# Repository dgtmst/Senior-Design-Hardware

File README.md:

# Senior-Design-Hardware
Repository for the hardware side of the senior design project
Will primarily be used for PCB design, could use it for other things later

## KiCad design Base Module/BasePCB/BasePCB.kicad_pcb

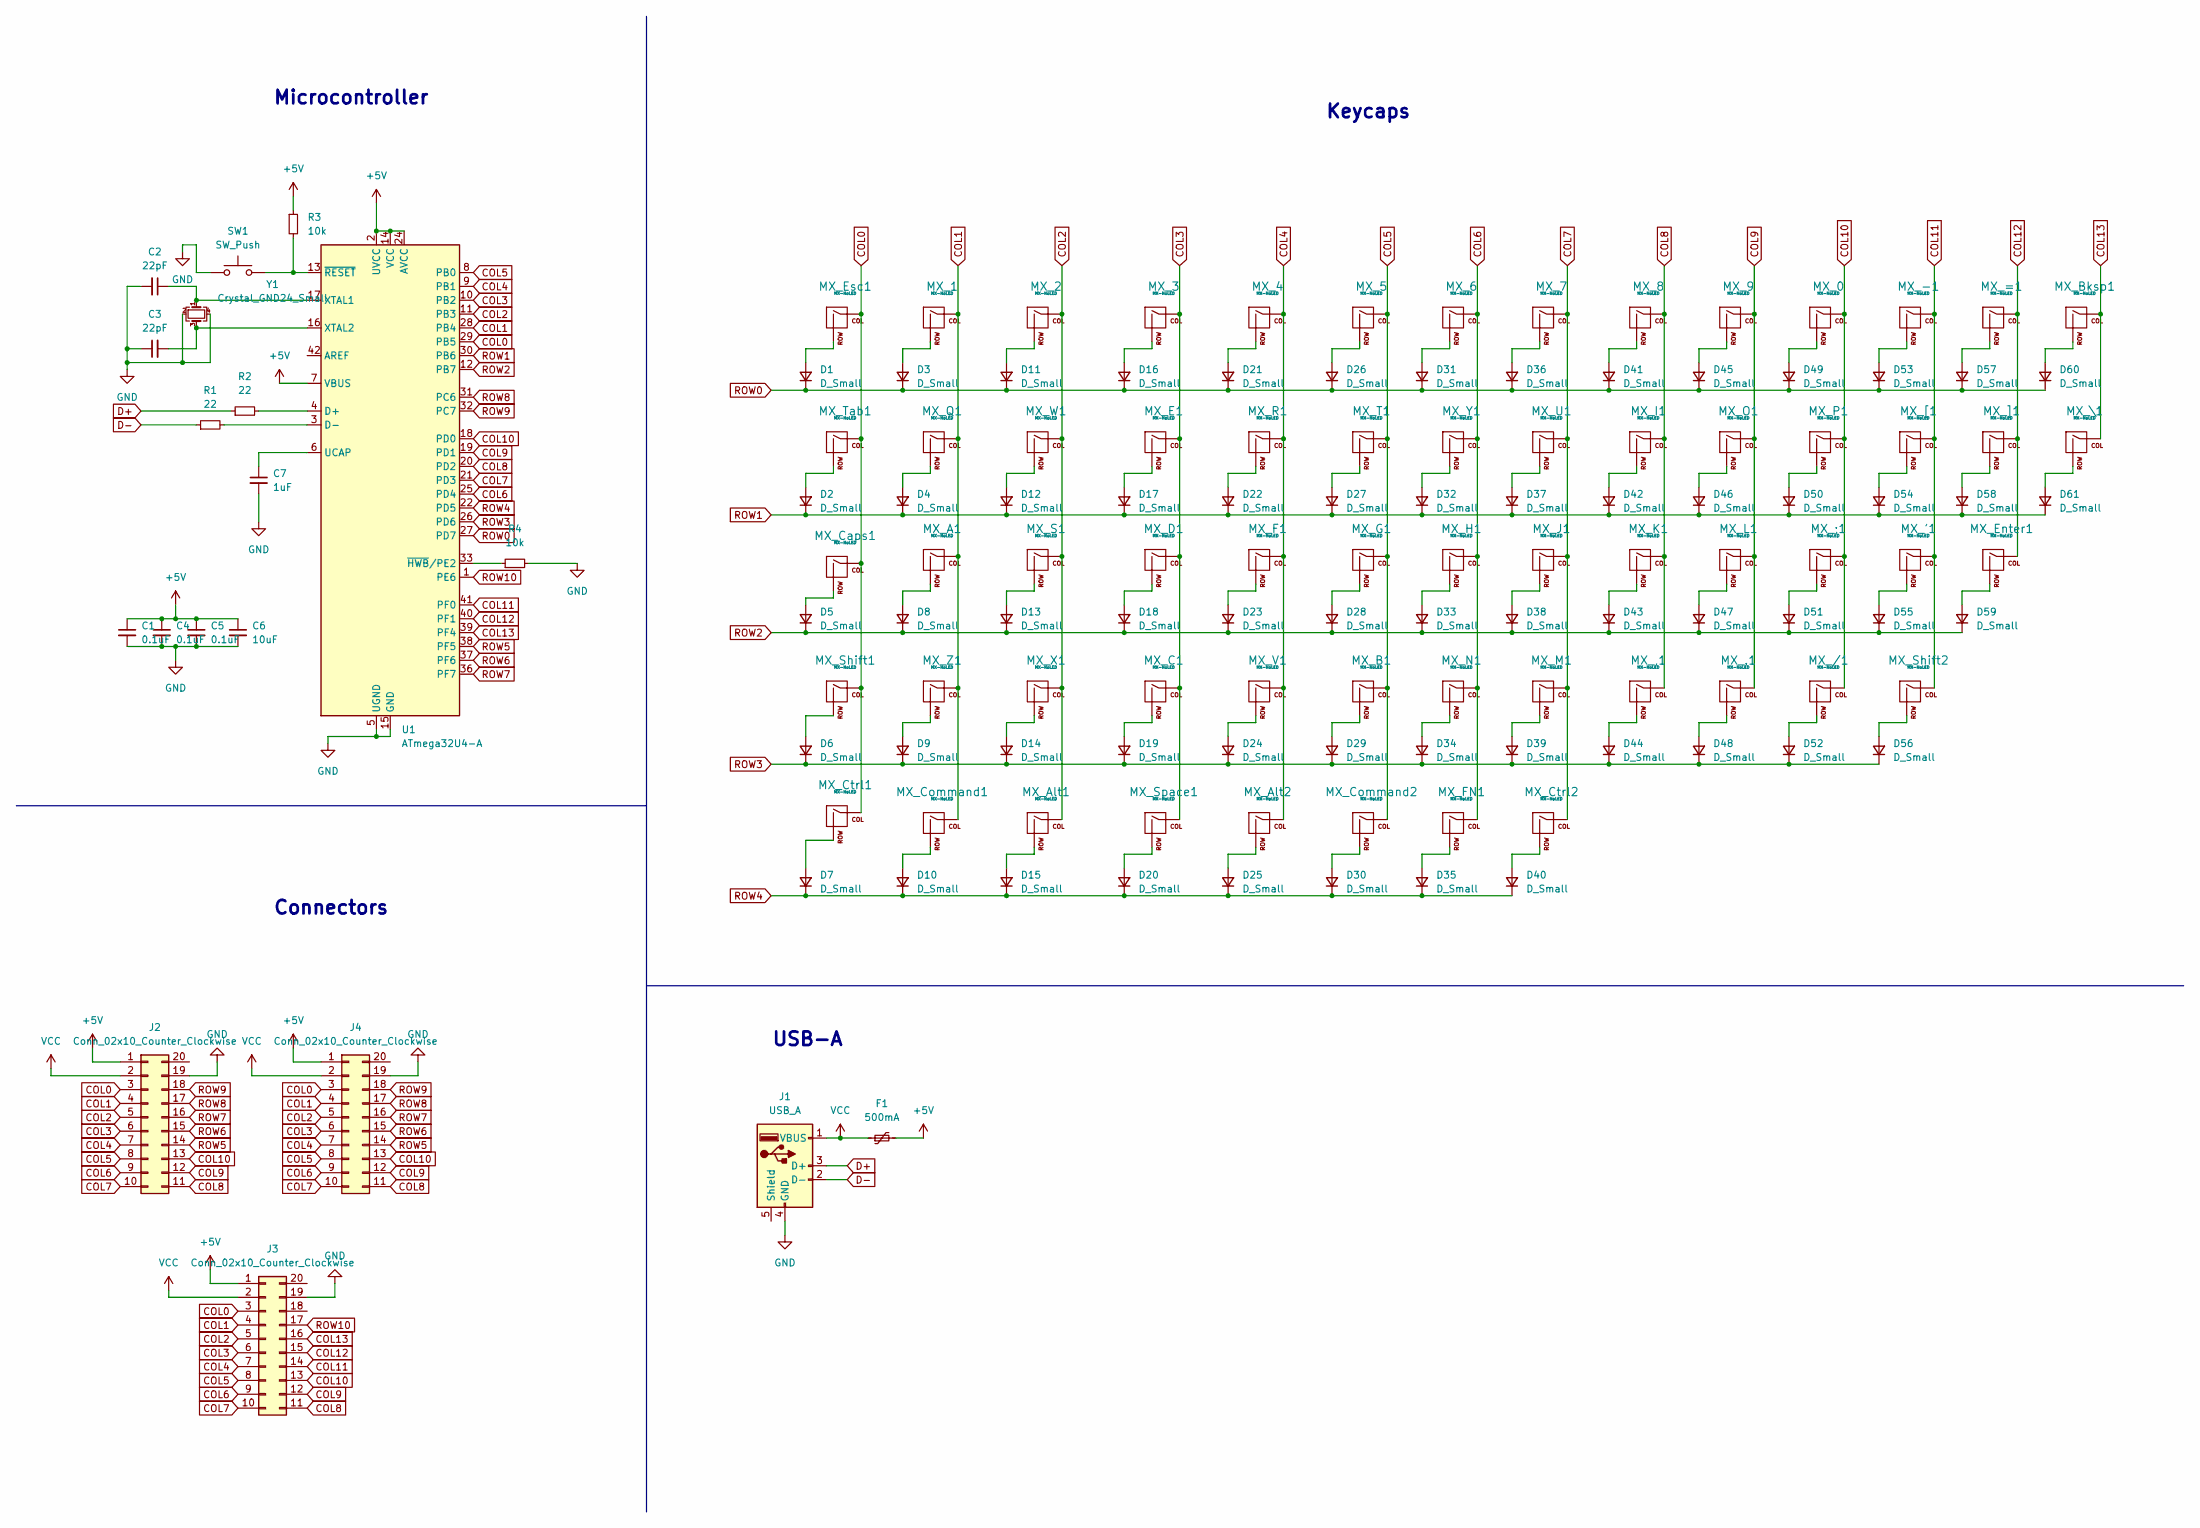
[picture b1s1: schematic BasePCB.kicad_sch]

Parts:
C1, C4, C5: 0.1uF; C_0805_2012Metric
C2, C3: 22pF; C_0805_2012Metric
C6: 10uF; C_0805_2012Metric
C7: 1uF; C_0805_2012Metric
D1, D2, D3, D4, D5, D6, D7, D8, D9, D10, D11, D12, D13, D14, D15, D16, D17, D18, D19, D20, D21, D22, D23, D24, D25, D26, D27, D28, D29, D30, D31, D32, D33, D34, D35, D36, D37, D38, D39, D40, D41, D42, D43, D44, D45, D46, D47, D48, D49, D50, D51, D52, D53, D54, D55, D56, D57, D58, D59, D60, D61: D_Small; D_SOD-123
F1: 500mA; Fuse_1206_3216Metric
J1: USB_A; USB-A-Generic
J2, J3: Conn_02x10_Counter_Clockwise; PinSocket_2x10_P2.54mm_Horizontal
J4: Conn_02x10_Counter_Clockwise; PinHeader_2x10_P2.54mm_Horizontal
MX_0, MX_1, MX_2, MX_3, MX_4, MX_5, MX_6, MX_7, MX_8, MX_9, MX_.1: MX-NoLED; MX-1U-NoLED
MX_'1: MX-NoLED; MX-1U-NoLED
MX_,1: MX-NoLED; MX-1U-NoLED
MX_-1: MX-NoLED; MX-1U-NoLED
MX_/1: MX-NoLED; MX-1U-NoLED
MX_;1: MX-NoLED; MX-1U-NoLED
MX_=1: MX-NoLED; MX-1U-NoLED
MX_A1: MX-NoLED; MX-1U-NoLED
MX_Alt1, MX_Alt2: MX-NoLED; MX-1U-NoLED
MX_B1: MX-NoLED; MX-1U-NoLED
MX_Bksp1: MX-NoLED; MX-1U-NoLED
MX_C1: MX-NoLED; MX-1U-NoLED
MX_Caps1: MX-NoLED; MX-1U-NoLED
MX_Command1, MX_Command2: MX-NoLED; MX-1U-NoLED
MX_Ctrl1, MX_Ctrl2: MX-NoLED; MX-1U-NoLED
MX_D1: MX-NoLED; MX-1U-NoLED
MX_E1: MX-NoLED; MX-1U-NoLED
MX_Enter1: MX-NoLED; MX-1U-NoLED
MX_Esc1: MX-NoLED; MX-1U-NoLED
MX_F1: MX-NoLED; MX-1U-NoLED
MX_FN1: MX-NoLED; MX-1U-NoLED
MX_G1: MX-NoLED; MX-1U-NoLED
MX_H1: MX-NoLED; MX-1U-NoLED
MX_I1: MX-NoLED; MX-1U-NoLED
MX_J1: MX-NoLED; MX-1U-NoLED
MX_K1: MX-NoLED; MX-1U-NoLED
MX_L1: MX-NoLED; MX-1U-NoLED
MX_M1: MX-NoLED; MX-1U-NoLED
MX_N1: MX-NoLED; MX-1U-NoLED
MX_O1: MX-NoLED; MX-1U-NoLED
MX_P1: MX-NoLED; MX-1U-NoLED
MX_Q1: MX-NoLED; MX-1U-NoLED
MX_R1: MX-NoLED; MX-1U-NoLED
MX_S1: MX-NoLED; MX-1U-NoLED
MX_Shift1, MX_Shift2: MX-NoLED; MX-1U-NoLED
MX_Space1: MX-NoLED; MX-1U-NoLED
MX_T1: MX-NoLED; MX-1U-NoLED
MX_Tab1: MX-NoLED; MX-1U-NoLED
MX_U1: MX-NoLED; MX-1U-NoLED
MX_V1: MX-NoLED; MX-1U-NoLED
MX_W1: MX-NoLED; MX-1U-NoLED
MX_X1: MX-NoLED; MX-1U-NoLED
MX_Y1: MX-NoLED; MX-1U-NoLED
MX_Z1: MX-NoLED; MX-1U-NoLED
MX_[1: MX-NoLED; MX-1U-NoLED
MX_\1: MX-NoLED; MX-1U-NoLED
MX_]1: MX-NoLED; MX-1U-NoLED
R1, R2: 22; R_0805_2012Metric
R3, R4: 10k; R_0805_2012Metric
SW1: SW_Push; SKQG-1155865
U1: ATmega32U4-A; TQFP-44_10x10mm_P0.8mm
Y1: Crystal_GND24_Small; Crystal_SMD_3225-4Pin_3.2x2.5mm

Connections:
+5V: C1.1, C4.1, C5.1, C6.1, F1.2, J2.1, J3.1, J4.1, R3.1, U1.2 (UVCC), U1.7 (VBUS), U1.14 (VCC), U1.24 (AVCC), U1.34 (VCC), U1.44 (AVCC)
COL0: J2.3, J3.3, J4.3, MX_Caps1.1 (COL), MX_Ctrl1.1 (COL), MX_Esc1.1 (COL), MX_Shift1.1 (COL), MX_Tab1.1 (COL), U1.29 (PB5)
COL1: J2.4, J3.4, J4.4, MX_1.1 (COL), MX_A1.1 (COL), MX_Command1.1 (COL), MX_Q1.1 (COL), MX_Z1.1 (COL), U1.28 (PB4)
COL2: J2.5, J3.5, J4.5, MX_2.1 (COL), MX_Alt1.1 (COL), MX_S1.1 (COL), MX_W1.1 (COL), MX_X1.1 (COL), U1.11 (PB3)
COL3: J2.6, J3.6, J4.6, MX_3.1 (COL), MX_C1.1 (COL), MX_D1.1 (COL), MX_E1.1 (COL), MX_Space1.1 (COL), U1.10 (PB2)
COL4: J2.7, J3.7, J4.7, MX_4.1 (COL), MX_Alt2.1 (COL), MX_F1.1 (COL), MX_R1.1 (COL), MX_V1.1 (COL), U1.9 (PB1)
COL5: J2.8, J3.8, J4.8, MX_5.1 (COL), MX_B1.1 (COL), MX_Command2.1 (COL), MX_G1.1 (COL), MX_T1.1 (COL), U1.8 (PB0)
COL6: J2.9, J3.9, J4.9, MX_6.1 (COL), MX_FN1.1 (COL), MX_H1.1 (COL), MX_N1.1 (COL), MX_Y1.1 (COL), U1.25 (PD4)
COL7: J2.10, J3.10, J4.10, MX_7.1 (COL), MX_Ctrl2.1 (COL), MX_J1.1 (COL), MX_M1.1 (COL), MX_U1.1 (COL), U1.21 (PD3)
COL8: J2.11, J3.11, J4.11, MX_8.1 (COL), MX_,1.1 (COL), MX_I1.1 (COL), MX_K1.1 (COL), U1.20 (PD2)
COL9: J2.12, J3.12, J4.12, MX_9.1 (COL), MX_.1.1 (COL), MX_L1.1 (COL), MX_O1.1 (COL), U1.19 (PD1)
COL10: J2.13, J3.13, J4.13, MX_0.1 (COL), MX_/1.1 (COL), MX_;1.1 (COL), MX_P1.1 (COL), U1.18 (PD0)
COL11: J3.14, MX_'1.1 (COL), MX_-1.1 (COL), MX_Shift2.1 (COL), MX_[1.1 (COL), U1.41 (PF0)
COL12: J3.15, MX_=1.1 (COL), MX_Enter1.1 (COL), MX_]1.1 (COL), U1.40 (PF1)
COL13: J3.16, MX_Bksp1.1 (COL), MX_\1.1 (COL), U1.39 (PF4)
D+: J1.3 (D+), R2.1
D-: J1.2 (D-), R1.1
GND: C1.2, C2.2, C3.1, C4.2, C5.2, C6.2, C7.2, J1.4 (GND), J2.19, J3.19, J4.19, R4.2, SW1.1, U1.5 (UGND), U1.15 (GND), U1.23 (GND), U1.35 (GND), U1.43 (GND), Y1.2, Y1.4
unnamed: C2.1, U1.17 (XTAL1), Y1.1
unnamed: C3.2, U1.16 (XTAL2), Y1.3
unnamed: C7.1, U1.6 (UCAP)
unnamed: D1.2 (A), MX_Esc1.2 (ROW)
unnamed: D2.2 (A), MX_Tab1.2 (ROW)
unnamed: D3.2 (A), MX_1.2 (ROW)
unnamed: D4.2 (A), MX_Q1.2 (ROW)
unnamed: D5.2 (A), MX_Caps1.2 (ROW)
unnamed: D6.2 (A), MX_Shift1.2 (ROW)
unnamed: D7.2 (A), MX_Ctrl1.2 (ROW)
unnamed: D8.2 (A), MX_A1.2 (ROW)
unnamed: D9.2 (A), MX_Z1.2 (ROW)
unnamed: D10.2 (A), MX_Command1.2 (ROW)
unnamed: D11.2 (A), MX_2.2 (ROW)
unnamed: D12.2 (A), MX_W1.2 (ROW)
unnamed: D13.2 (A), MX_S1.2 (ROW)
unnamed: D14.2 (A), MX_X1.2 (ROW)
unnamed: D15.2 (A), MX_Alt1.2 (ROW)
unnamed: D16.2 (A), MX_3.2 (ROW)
unnamed: D17.2 (A), MX_E1.2 (ROW)
unnamed: D18.2 (A), MX_D1.2 (ROW)
unnamed: D19.2 (A), MX_C1.2 (ROW)
unnamed: D20.2 (A), MX_Space1.2 (ROW)
unnamed: D21.2 (A), MX_4.2 (ROW)
unnamed: D22.2 (A), MX_R1.2 (ROW)
unnamed: D23.2 (A), MX_F1.2 (ROW)
unnamed: D24.2 (A), MX_V1.2 (ROW)
unnamed: D25.2 (A), MX_Alt2.2 (ROW)
unnamed: D26.2 (A), MX_5.2 (ROW)
unnamed: D27.2 (A), MX_T1.2 (ROW)
unnamed: D28.2 (A), MX_G1.2 (ROW)
unnamed: D29.2 (A), MX_B1.2 (ROW)
unnamed: D30.2 (A), MX_Command2.2 (ROW)
unnamed: D31.2 (A), MX_6.2 (ROW)
unnamed: D32.2 (A), MX_Y1.2 (ROW)
unnamed: D33.2 (A), MX_H1.2 (ROW)
unnamed: D34.2 (A), MX_N1.2 (ROW)
unnamed: D35.2 (A), MX_FN1.2 (ROW)
unnamed: D36.2 (A), MX_7.2 (ROW)
unnamed: D37.2 (A), MX_U1.2 (ROW)
unnamed: D38.2 (A), MX_J1.2 (ROW)
unnamed: D39.2 (A), MX_M1.2 (ROW)
unnamed: D40.2 (A), MX_Ctrl2.2 (ROW)
unnamed: D41.2 (A), MX_8.2 (ROW)
unnamed: D42.2 (A), MX_I1.2 (ROW)
unnamed: D43.2 (A), MX_K1.2 (ROW)
unnamed: D44.2 (A), MX_,1.2 (ROW)
unnamed: D45.2 (A), MX_9.2 (ROW)
unnamed: D46.2 (A), MX_O1.2 (ROW)
unnamed: D47.2 (A), MX_L1.2 (ROW)
unnamed: D48.2 (A), MX_.1.2 (ROW)
unnamed: D49.2 (A), MX_0.2 (ROW)
unnamed: D50.2 (A), MX_P1.2 (ROW)
unnamed: D51.2 (A), MX_;1.2 (ROW)
unnamed: D52.2 (A), MX_/1.2 (ROW)
unnamed: D53.2 (A), MX_-1.2 (ROW)
unnamed: D54.2 (A), MX_[1.2 (ROW)
unnamed: D55.2 (A), MX_'1.2 (ROW)
unnamed: D56.2 (A), MX_Shift2.2 (ROW)
unnamed: D57.2 (A), MX_=1.2 (ROW)
unnamed: D58.2 (A), MX_]1.2 (ROW)
unnamed: D59.2 (A), MX_Enter1.2 (ROW)
unnamed: D60.2 (A), MX_Bksp1.2 (ROW)
unnamed: D61.2 (A), MX_\1.2 (ROW)
unnamed: R1.2, U1.3 (D-)
unnamed: R2.2, U1.4 (D+)
unnamed: R3.2, SW1.2, U1.13 (~RESET)
unnamed: R4.1, U1.33 (~HWB/PE2)
ROW0: D1.1 (K), D3.1 (K), D11.1 (K), D16.1 (K), D21.1 (K), D26.1 (K), D31.1 (K), D36.1 (K), D41.1 (K), D45.1 (K), D49.1 (K), D53.1 (K), D57.1 (K), D60.1 (K), U1.27 (PD7)
ROW1: D2.1 (K), D4.1 (K), D12.1 (K), D17.1 (K), D22.1 (K), D27.1 (K), D32.1 (K), D37.1 (K), D42.1 (K), D46.1 (K), D50.1 (K), D54.1 (K), D58.1 (K), D61.1 (K), U1.30 (PB6)
ROW2: D5.1 (K), D8.1 (K), D13.1 (K), D18.1 (K), D23.1 (K), D28.1 (K), D33.1 (K), D38.1 (K), D43.1 (K), D47.1 (K), D51.1 (K), D55.1 (K), D59.1 (K), U1.12 (PB7)
ROW3: D6.1 (K), D9.1 (K), D14.1 (K), D19.1 (K), D24.1 (K), D29.1 (K), D34.1 (K), D39.1 (K), D44.1 (K), D48.1 (K), D52.1 (K), D56.1 (K), U1.26 (PD6)
ROW4: D7.1 (K), D10.1 (K), D15.1 (K), D20.1 (K), D25.1 (K), D30.1 (K), D35.1 (K), D40.1 (K), U1.22 (PD5)
ROW5: J2.14, J4.14, U1.38 (PF5)
ROW6: J2.15, J4.15, U1.37 (PF6)
ROW7: J2.16, J4.16, U1.36 (PF7)
ROW8: J2.17, J4.17, U1.31 (PC6)
ROW9: J2.18, J4.18, U1.32 (PC7)
ROW10: J3.17, U1.1 (PE6)
VCC: F1.1, J1.1 (VBUS), J2.2, J3.2, J4.2

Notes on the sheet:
USB-A
Keycaps
Connectors
Microcontroller

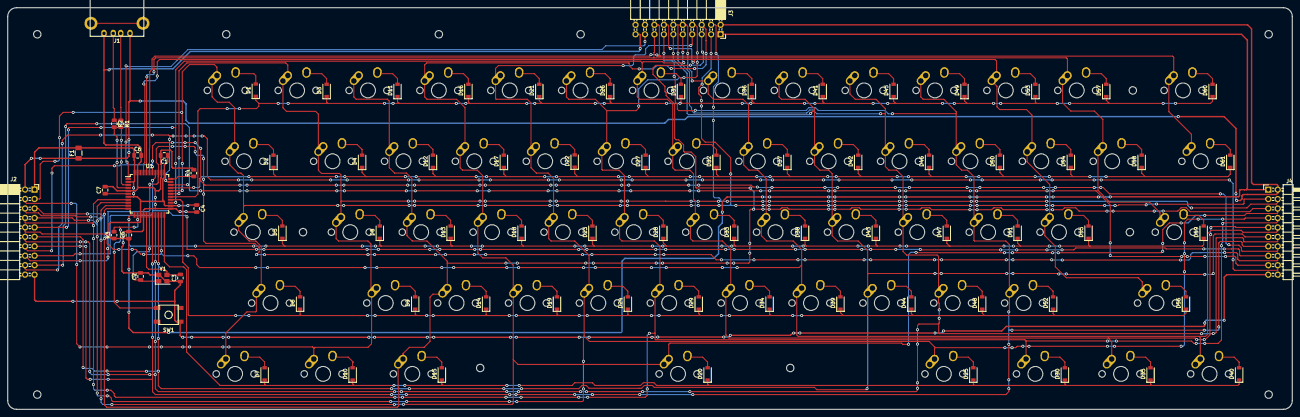
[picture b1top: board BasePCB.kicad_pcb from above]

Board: 2 copper layers, 345.3 x 108.0 mm, 141 parts (0 on the bottom side), 98 nets.

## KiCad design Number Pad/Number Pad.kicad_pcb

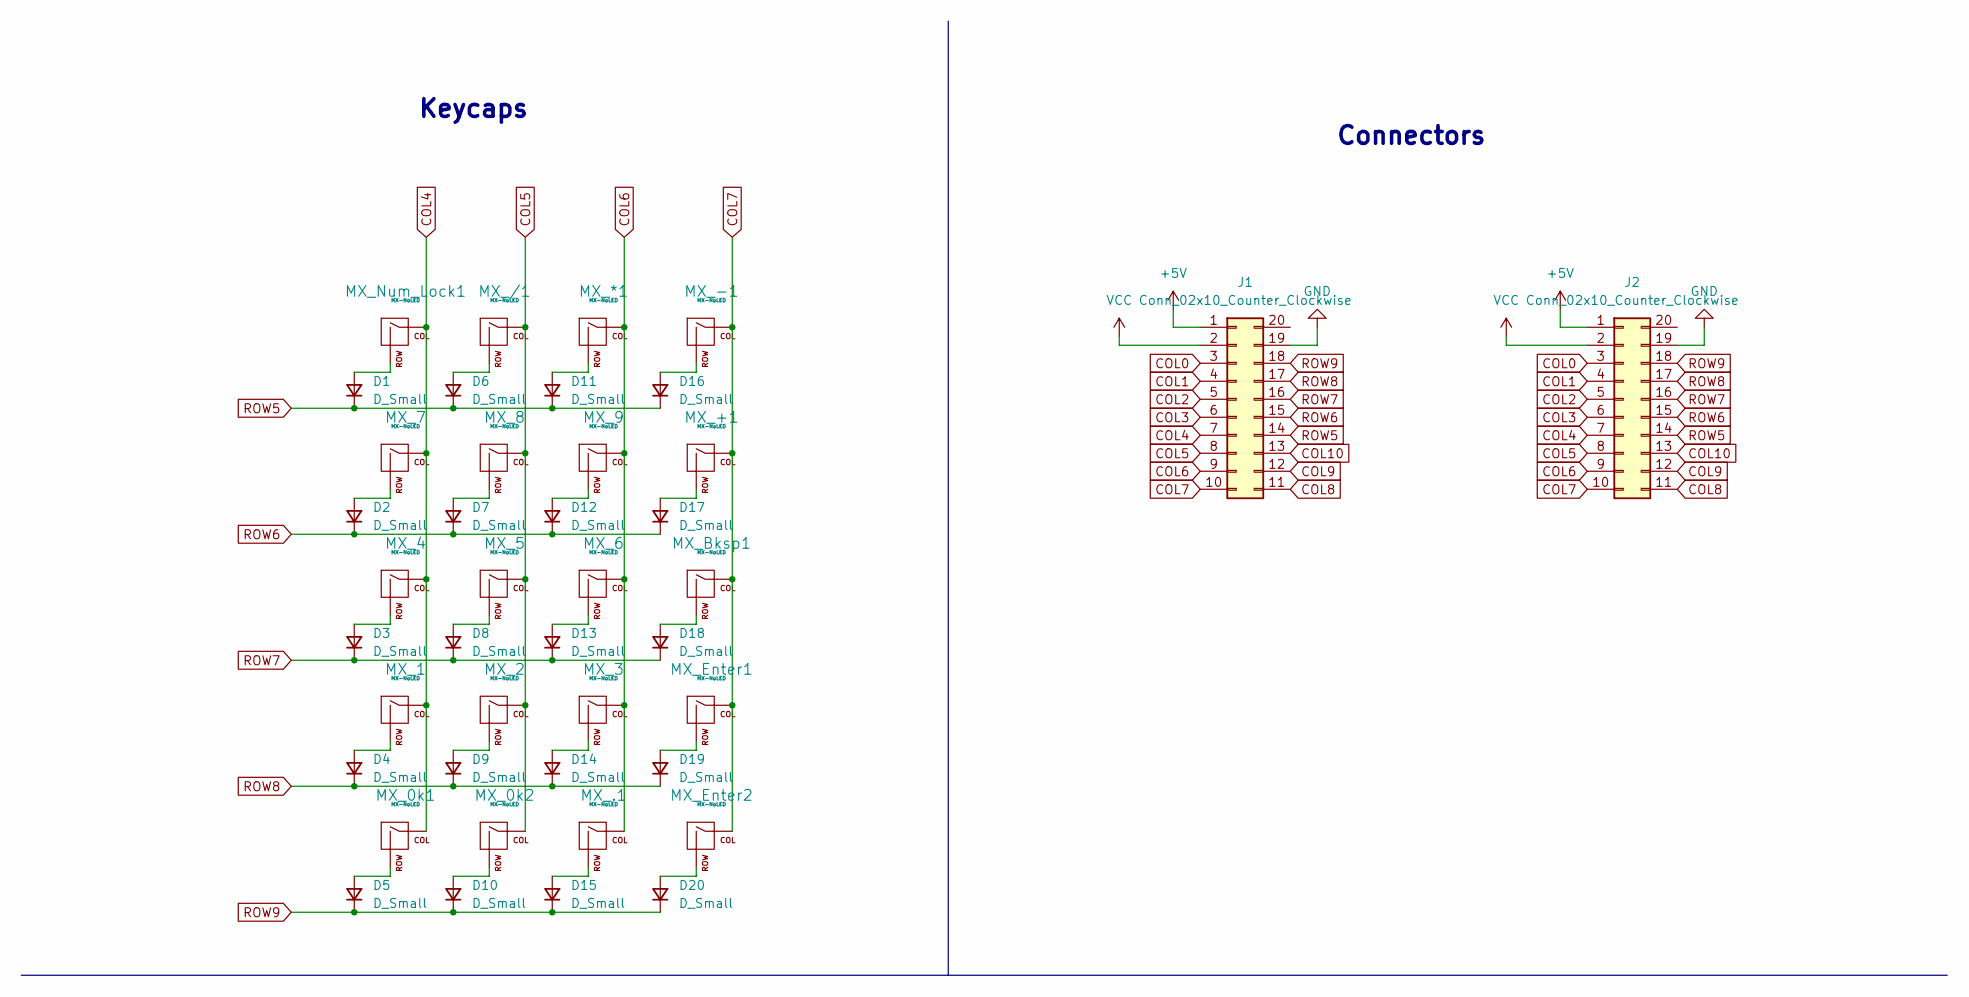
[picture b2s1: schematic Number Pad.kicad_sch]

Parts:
D1, D2, D3, D4, D5, D6, D7, D8, D9, D10, D11, D12, D13, D14, D15, D16, D17, D18, D19, D20: D_Small; D_SOD-123
J1: Conn_02x10_Counter_Clockwise; PinHeader_2x10_P2.54mm_Horizontal
J2: Conn_02x10_Counter_Clockwise; PinSocket_2x10_P2.54mm_Horizontal
MX_0k1, MX_0k2, MX_1, MX_2, MX_3, MX_4, MX_5, MX_6, MX_7, MX_8, MX_9, MX_.1: MX-NoLED; MX-1U-NoLED
MX_*1: MX-NoLED; MX-1U-NoLED
MX_+1: MX-NoLED; MX-1U-NoLED
MX_-1: MX-NoLED; MX-1U-NoLED
MX_/1: MX-NoLED; MX-1U-NoLED
MX_Bksp1: MX-NoLED; MX-1U-NoLED
MX_Enter1, MX_Enter2: MX-NoLED; MX-1U-NoLED
MX_Num_Lock1: MX-NoLED; MX-1U-NoLED

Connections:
+5V: J1.1, J2.1
COL0: J1.3, J2.3
COL1: J1.4, J2.4
COL2: J1.5, J2.5
COL3: J1.6, J2.6
COL4: J1.7, J2.7, MX_0k1.1 (COL), MX_1.1 (COL), MX_4.1 (COL), MX_7.1 (COL), MX_Num_Lock1.1 (COL)
COL5: J1.8, J2.8, MX_0k2.1 (COL), MX_2.1 (COL), MX_5.1 (COL), MX_8.1 (COL), MX_/1.1 (COL)
COL6: J1.9, J2.9, MX_3.1 (COL), MX_6.1 (COL), MX_9.1 (COL), MX_*1.1 (COL), MX_.1.1 (COL)
COL7: J1.10, J2.10, MX_+1.1 (COL), MX_-1.1 (COL), MX_Bksp1.1 (COL), MX_Enter1.1 (COL), MX_Enter2.1 (COL)
COL8: J1.11, J2.11
COL9: J1.12, J2.12
COL10: J1.13, J2.13
GND: J1.19, J2.19
unnamed: D1.2 (A), MX_Num_Lock1.2 (ROW)
unnamed: D2.2 (A), MX_7.2 (ROW)
unnamed: D3.2 (A), MX_4.2 (ROW)
unnamed: D4.2 (A), MX_1.2 (ROW)
unnamed: D5.2 (A), MX_0k1.2 (ROW)
unnamed: D6.2 (A), MX_/1.2 (ROW)
unnamed: D7.2 (A), MX_8.2 (ROW)
unnamed: D8.2 (A), MX_5.2 (ROW)
unnamed: D9.2 (A), MX_2.2 (ROW)
unnamed: D10.2 (A), MX_0k2.2 (ROW)
unnamed: D11.2 (A), MX_*1.2 (ROW)
unnamed: D12.2 (A), MX_9.2 (ROW)
unnamed: D13.2 (A), MX_6.2 (ROW)
unnamed: D14.2 (A), MX_3.2 (ROW)
unnamed: D15.2 (A), MX_.1.2 (ROW)
unnamed: D16.2 (A), MX_-1.2 (ROW)
unnamed: D17.2 (A), MX_+1.2 (ROW)
unnamed: D18.2 (A), MX_Bksp1.2 (ROW)
unnamed: D19.2 (A), MX_Enter1.2 (ROW)
unnamed: D20.2 (A), MX_Enter2.2 (ROW)
ROW5: D1.1 (K), D6.1 (K), D11.1 (K), D16.1 (K), J1.14, J2.14
ROW6: D2.1 (K), D7.1 (K), D12.1 (K), D17.1 (K), J1.15, J2.15
ROW7: D3.1 (K), D8.1 (K), D13.1 (K), D18.1 (K), J1.16, J2.16
ROW8: D4.1 (K), D9.1 (K), D14.1 (K), D19.1 (K), J1.17, J2.17
ROW9: D5.1 (K), D10.1 (K), D15.1 (K), D20.1 (K), J1.18, J2.18
VCC: J1.2, J2.2

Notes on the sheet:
Keycaps
Connectors

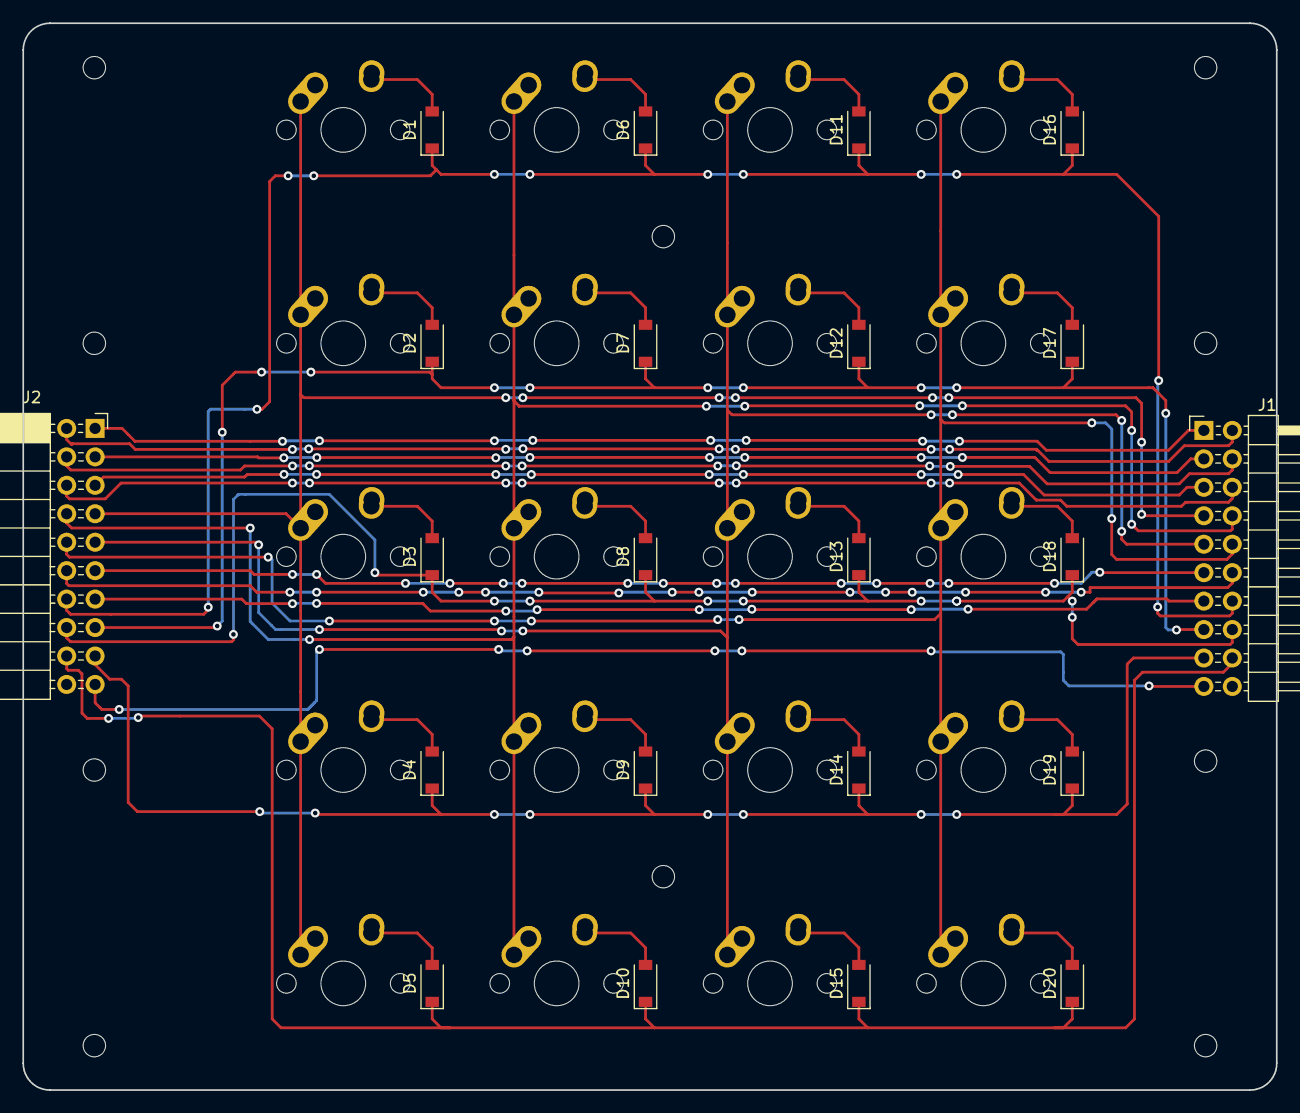
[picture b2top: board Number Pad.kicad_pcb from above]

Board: 2 copper layers, 111.9 x 95.2 mm, 42 parts (0 on the bottom side), 39 nets.

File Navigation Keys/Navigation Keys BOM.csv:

"Id";"Designator";"Package";"Quantity";"Designation";"Supplier and ref";
1;"D2,D1,D3,D4,D10,D5,D6,D7,D9,D8";"D_SOD-123";10;"D_Small";;;
2;"MX_Right1,MX_Insr1,MX_Pg_Up1,MX_Home1,MX_Left1,MX_Dlt1,MX_End1,MX_Pg_Dwn1,MX_Up1,MX_Down1";"MX-1U-NoLED";10;"MX-NoLED";;;
3;"J2";"PinHeader_2x10_P2.54mm_Horizontal";1;"Conn_02x10_Counter_Clockwise";;;
4;"J1";"PinSocket_2x10_P2.54mm_Horizontal";1;"Conn_02x10_Counter_Clockwise";;;

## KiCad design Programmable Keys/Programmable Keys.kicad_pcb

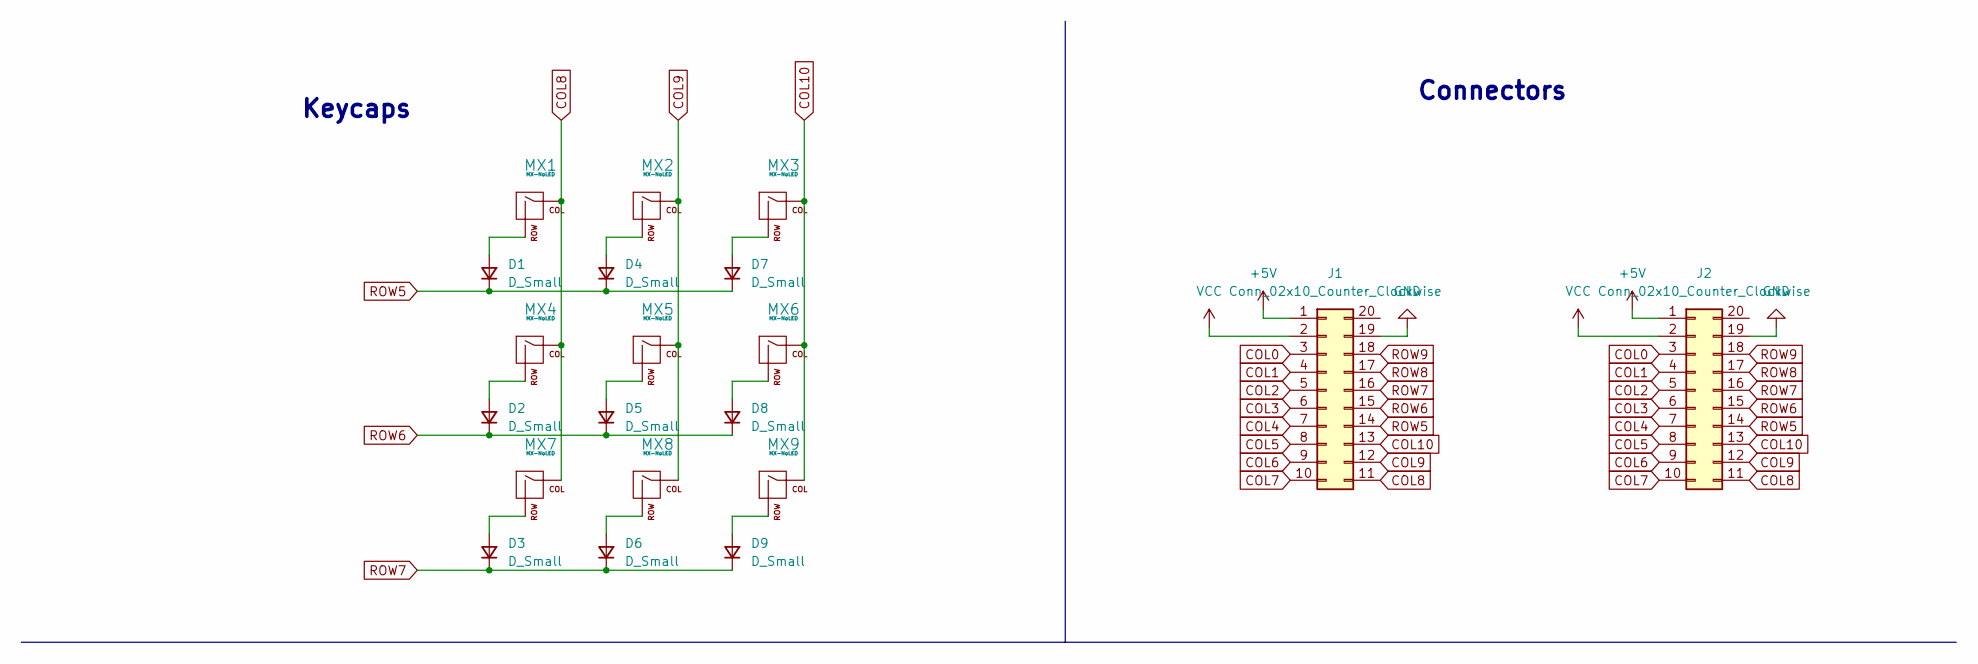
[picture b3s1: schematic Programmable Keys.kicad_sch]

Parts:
D1, D2, D3, D4, D5, D6, D7, D8, D9: D_Small; D_SOD-123
J1: Conn_02x10_Counter_Clockwise; PinSocket_2x10_P2.54mm_Horizontal
J2: Conn_02x10_Counter_Clockwise; PinHeader_2x10_P2.54mm_Horizontal
MX1, MX2, MX3, MX4, MX5, MX6, MX7, MX8, MX9: MX-NoLED; MX-1U-NoLED

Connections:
+5V: J1.1, J2.1
COL0: J1.3, J2.3
COL1: J1.4, J2.4
COL2: J1.5, J2.5
COL3: J1.6, J2.6
COL4: J1.7, J2.7
COL5: J1.8, J2.8
COL6: J1.9, J2.9
COL7: J1.10, J2.10
COL8: J1.11, J2.11, MX1.1 (COL), MX4.1 (COL), MX7.1 (COL)
COL9: J1.12, J2.12, MX2.1 (COL), MX5.1 (COL), MX8.1 (COL)
COL10: J1.13, J2.13, MX3.1 (COL), MX6.1 (COL), MX9.1 (COL)
GND: J1.19, J2.19
unnamed: D1.2 (A), MX1.2 (ROW)
unnamed: D2.2 (A), MX4.2 (ROW)
unnamed: D3.2 (A), MX7.2 (ROW)
unnamed: D4.2 (A), MX2.2 (ROW)
unnamed: D5.2 (A), MX5.2 (ROW)
unnamed: D6.2 (A), MX8.2 (ROW)
unnamed: D7.2 (A), MX3.2 (ROW)
unnamed: D8.2 (A), MX6.2 (ROW)
unnamed: D9.2 (A), MX9.2 (ROW)
ROW5: D1.1 (K), D4.1 (K), D7.1 (K), J1.14, J2.14
ROW6: D2.1 (K), D5.1 (K), D8.1 (K), J1.15, J2.15
ROW7: D3.1 (K), D6.1 (K), D9.1 (K), J1.16, J2.16
ROW8: J1.17, J2.17
ROW9: J1.18, J2.18
VCC: J1.2, J2.2

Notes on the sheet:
Connectors
Keycaps

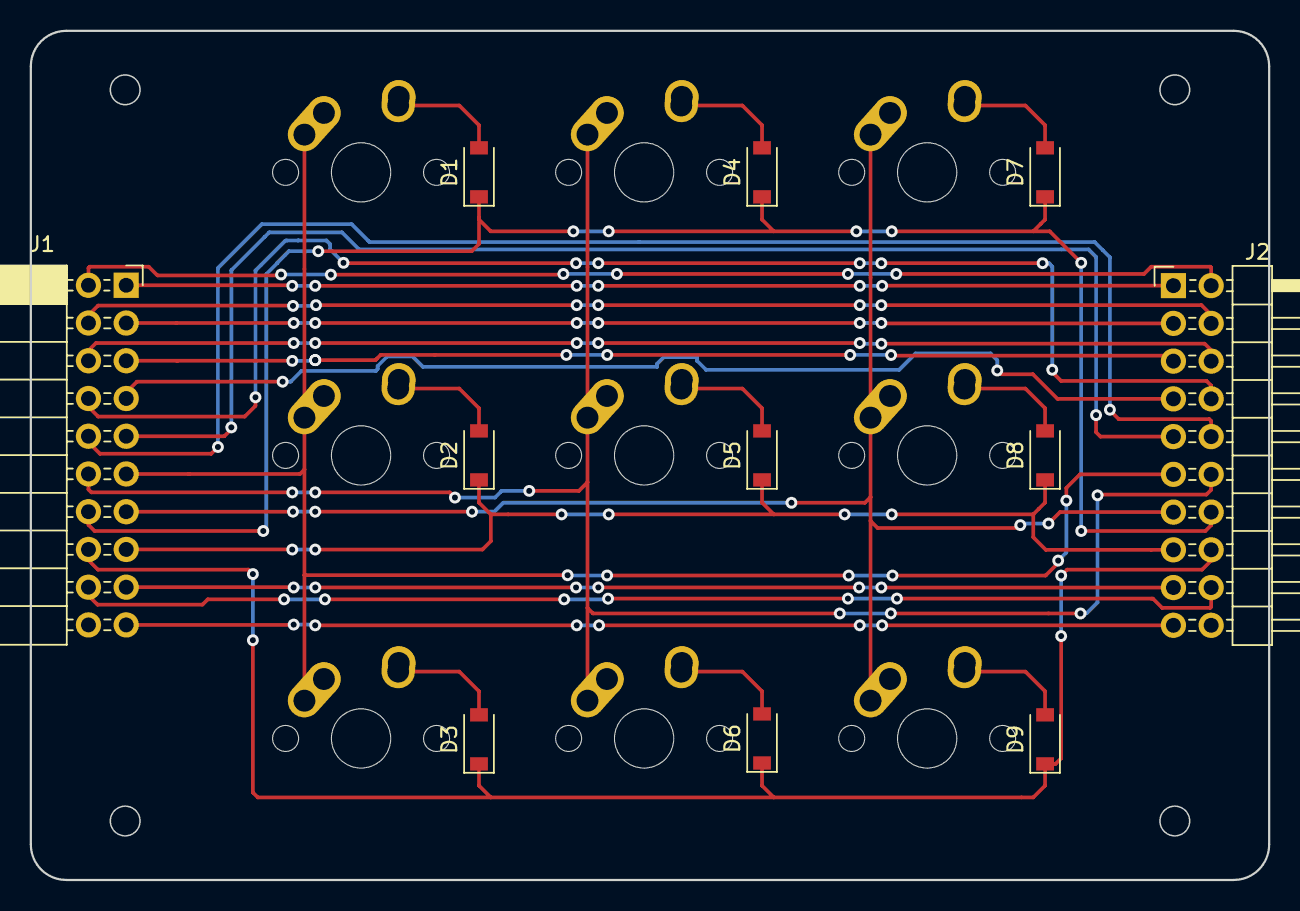
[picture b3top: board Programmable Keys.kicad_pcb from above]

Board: 2 copper layers, 83.3 x 57.1 mm, 20 parts (0 on the bottom side), 28 nets.

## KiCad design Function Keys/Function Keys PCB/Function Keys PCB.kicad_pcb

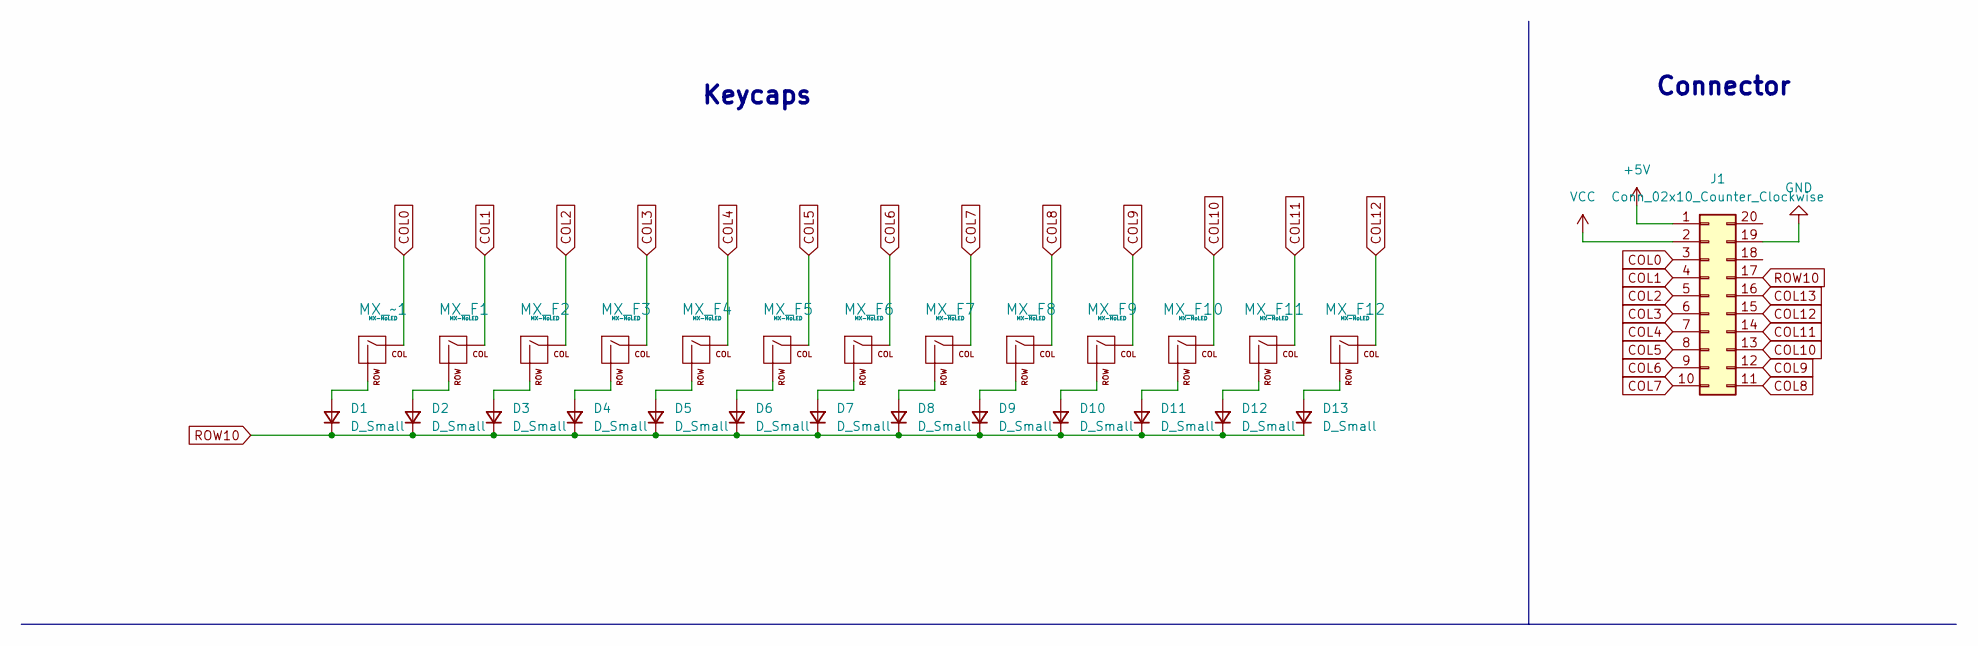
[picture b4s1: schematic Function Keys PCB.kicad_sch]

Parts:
D1, D2, D3, D4, D5, D6, D7, D8, D9, D10, D11, D12, D13: D_Small; D_SOD-123
J1: Conn_02x10_Counter_Clockwise; PinHeader_2x10_P2.54mm_Horizontal
MX_F1, MX_F2, MX_F3, MX_F4, MX_F5, MX_F6, MX_F7, MX_F8, MX_F9, MX_F10, MX_F11, MX_F12: MX-NoLED; MX-1U-NoLED
MX_~1: MX-NoLED; MX-1U-NoLED

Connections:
+5V: J1.1
COL0: J1.3, MX_~1.1 (COL)
COL1: J1.4, MX_F1.1 (COL)
COL2: J1.5, MX_F2.1 (COL)
COL3: J1.6, MX_F3.1 (COL)
COL4: J1.7, MX_F4.1 (COL)
COL5: J1.8, MX_F5.1 (COL)
COL6: J1.9, MX_F6.1 (COL)
COL7: J1.10, MX_F7.1 (COL)
COL8: J1.11, MX_F8.1 (COL)
COL9: J1.12, MX_F9.1 (COL)
COL10: J1.13, MX_F10.1 (COL)
COL11: J1.14, MX_F11.1 (COL)
COL12: J1.15, MX_F12.1 (COL)
COL13: J1.16
GND: J1.19
unnamed: D1.2 (A), MX_~1.2 (ROW)
unnamed: D2.2 (A), MX_F1.2 (ROW)
unnamed: D3.2 (A), MX_F2.2 (ROW)
unnamed: D4.2 (A), MX_F3.2 (ROW)
unnamed: D5.2 (A), MX_F4.2 (ROW)
unnamed: D6.2 (A), MX_F5.2 (ROW)
unnamed: D7.2 (A), MX_F6.2 (ROW)
unnamed: D8.2 (A), MX_F7.2 (ROW)
unnamed: D9.2 (A), MX_F8.2 (ROW)
unnamed: D10.2 (A), MX_F9.2 (ROW)
unnamed: D11.2 (A), MX_F10.2 (ROW)
unnamed: D12.2 (A), MX_F11.2 (ROW)
unnamed: D13.2 (A), MX_F12.2 (ROW)
ROW10: D1.1 (K), D2.1 (K), D3.1 (K), D4.1 (K), D5.1 (K), D6.1 (K), D7.1 (K), D8.1 (K), D9.1 (K), D10.1 (K), D11.1 (K), D12.1 (K), D13.1 (K), J1.17
VCC: J1.2

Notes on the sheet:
Keycaps
Connector

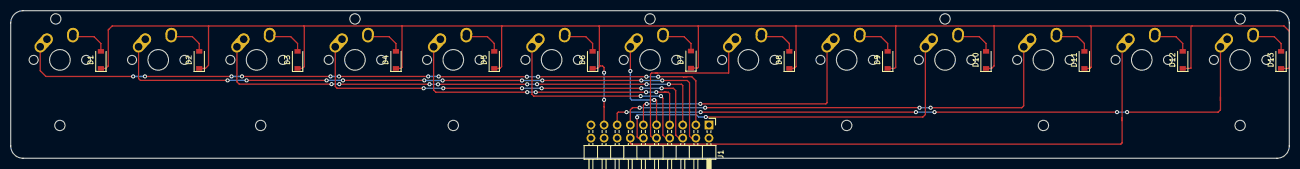
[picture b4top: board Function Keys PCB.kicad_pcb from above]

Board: 2 copper layers, 247.6 x 28.6 mm, 27 parts (0 on the bottom side), 27 nets.

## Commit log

2022-11-26 Created Kicad schematic
2022-11-26 Add submodules
2022-11-27 Added symbol libraries
2022-11-27 Added microcontroller to schematic
2022-11-27 Added to schematic
2022-11-27 Finished microcontroller
    On schematic
2022-11-27 Added switch matrix and USB
    not sure about USB A, might need to edit later
2022-11-27 Added and assigned footprints
2022-11-27 Started designing board
    placed components, started wiring
2022-11-27 Updated wiring
2022-11-28 Finished base module wiring
2022-12-01 Updated wiring a bit
2022-12-01 Updated schematic
    Added rest of keys to schematic
2022-12-01 Created schematic and PCB
2022-12-01 Added submodules
2022-12-01 Added keys to schematic
2022-12-01 Submodules
2022-12-01 Revert "Submodules"
    This reverts commit fa694d1800433122017d4f23c212003eb66935e9.
2022-12-01 Revert "Added submodules"
    This reverts commit cff3b9f090c0aee64a0c22bfa89b3e38b3e00d62.
2022-12-01 Created kicad files
2022-12-01 Added project libraries
2022-12-04 Added Connectors, labeled Keys
2022-12-04 Restored backup
    Accidentally deleted the kicad files and had to restore them. All good now (hopefully)
2022-12-04 Didn't change much
    nothing to note really
2022-12-06 Updated connectors, annotated schematic
2022-12-06 Assigned remaining footprints
2022-12-06 Added new components to PCB
2022-12-06 Added footprint libraries
2022-12-06 Updated schematic
2022-12-06 Assigned footprints
2022-12-07 Added connectors, labeled schematic
2022-12-07 Added footprints to library
2022-12-07 Added connectors, assigned footprints
2022-12-07 Started schematic
2022-12-08 Updated connectors
2022-12-08 Started on schematic
2022-12-08 Finished schematic placement, started wiring
2022-12-08 Continued wiring
2022-12-08 Added additional connector
2022-12-09 Finished wiring
2022-12-09 Made a few small changes
2022-12-09 Added potential new connectors
    might use them or not idfk bro
2022-12-09 Edited connectors a tad
2022-12-09 Started on component placement
2022-12-09 idk what this is
2022-12-09 Revert "Create Number Pad.kicad_prl"
    This reverts commit 8663c67909b50b6d7975b4a01d841de98d0ad9a6.
2022-12-09 Revert "idk what this is"
    This reverts commit 3165c2e8f72d5e2ef263d4ecf0f01ea3d2baf90f.
2022-12-09 Revert "Added potential new connectors"
    This reverts commit 86ebb0b8c096f4d7f87798976226ac9f3014035e.
2022-12-09 idk what I did but almost fucked shit up
    fixed it I hope
2022-12-09 Fixed issue with connector
    accidentally had two Vcc on each connector
2022-12-09 Started wiring
2022-12-09 Started part placement and wiring
2022-12-09 Edited connectors
2022-12-09 Continued wiring pcb
2022-12-09 Continued wiring pcb again
2022-12-09 Finished wiring, added grounded layer
2022-12-09 Fixed a few errors
2022-12-09 Updated connector
2022-12-09 Updated footprints
2022-12-09 Started placement / wiring
2022-12-09 Finished wiring / placement
2022-12-09 Added ground fill
2022-12-09 Updated connectors / footprint
2022-12-09 Updated connectors and footprints
2022-12-09 Finished routing
2022-12-09 Updated labels, schematic, and footprints
2022-12-09 Placed components
2022-12-09 Finished wiring and placement
2022-12-09 Added ground plane
2022-12-09 Restarted wiring
    Wiring was gonna be a pain so I decided to restart and do it better
2022-12-09 Finished pcb
    for now
2022-12-30 Generated Gerber Files
2022-12-30 Created Gerber Files
2023-01-13 Fixed Gerber Files
2023-03-06 Updated connectors and added through holes
2023-03-06 Updated conenctors
2023-03-06 Finished new connectors
2023-03-06 Updated connectors on schematic
2023-03-06 Finished connectors plus mounting holes
2023-03-06 Updated connectors + added mounting holes
2023-03-07 Updated mounting holes
2023-03-10 Generated new gerbers
2023-03-10 More gerber changes
2023-03-10 Updated gerbers / BOM
2023-03-13 Changed J3 ground pin and extended board
2023-03-13 Extended PCB for connectors
2023-03-13 Lengthened board & moved ground pin
2023-03-29 Fixed mounting hole size
2023-03-31 Changes mounting hole size
2023-03-31 Changed mounting hole size
2023-03-31 Updated mounting hole size
2023-04-03 Updated gerbers
2023-04-03 Created gerber zip file
2023-04-03 Generated new gerber files
